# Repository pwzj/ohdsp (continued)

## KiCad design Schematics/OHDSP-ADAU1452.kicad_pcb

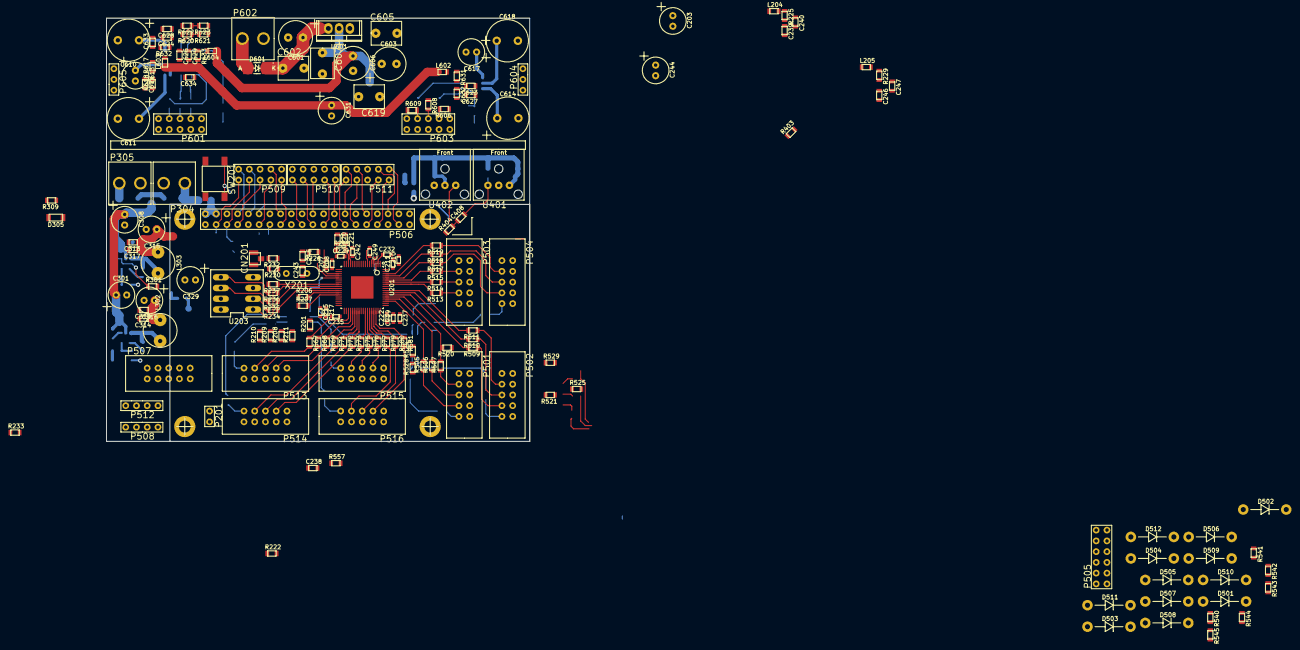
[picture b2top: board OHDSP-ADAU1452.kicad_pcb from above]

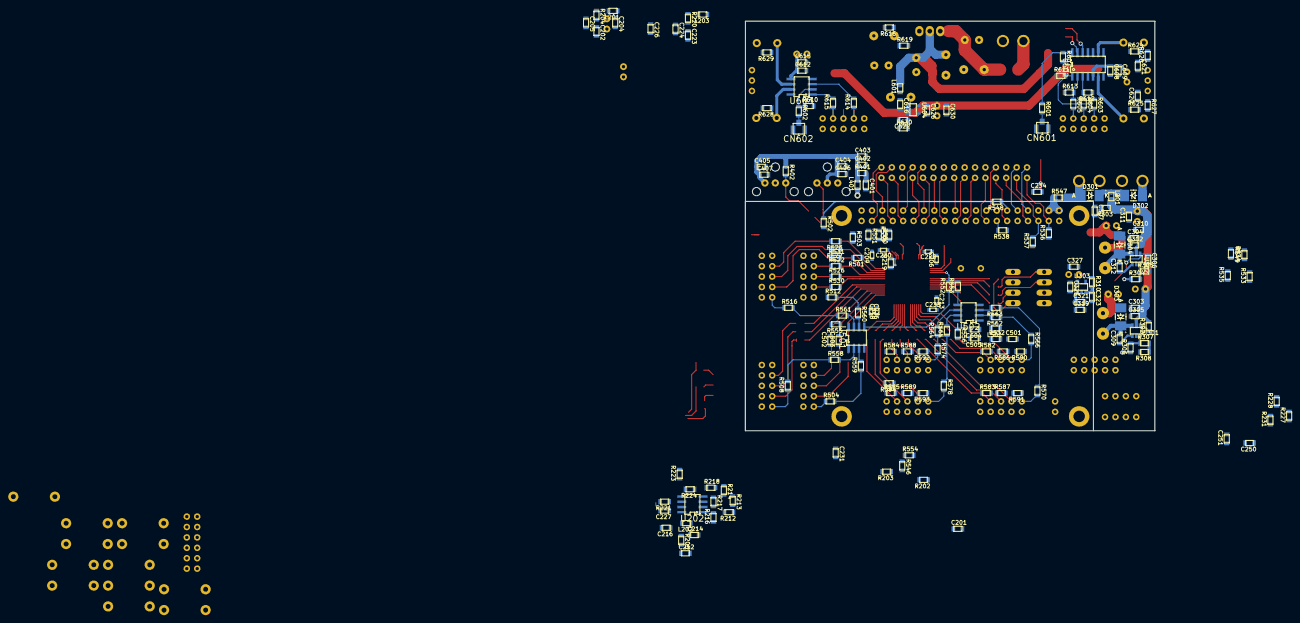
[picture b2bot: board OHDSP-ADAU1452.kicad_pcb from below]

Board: 4 copper layers, 100.0 x 100.0 mm, 376 parts (188 on the bottom side), 240 nets.

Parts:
C201, C205, C216, C226, C227, C231, C234, C238, C250, C304, C305, C311, C317, C318, C321, C325, C403, C406, C407, C503, C505, C604, C608, C612, C623, C624, C625, C626: 100n; SMD-0805
C202, C212, C223, C239, C246, C307, C401, C501, C632, C633, C634: 100p; SMD-0805
C203, C244, C301, C308, C315, C316, C329: 220u; CAP-TH-D6.3mmP2.5mm
C204, C224, C240, C247, C302, C303, C310, C313, C314, C319, C327, C402, C404, C405, C502, C504, C609, C615, C616, C627, C628, C629, C630: 22u; SMD-0805
C206, C209, C213, C218, C228, C230, C233, C236: 1u; SMD-0603
C207, C210, C215, C219, C229, C232, C235, C237, C242, C249: 100n; SMD-0603
C208, C211, C217, C222: 10n; SMD-0603
C214, C251, C306, C323: 1u; SMD-0805
C220: 5n6; SMD-0805
C221: 150p; SMD-0805
C243, C245: 33p; SMD-0805
C309, C312, C408, C622: 10n; SMD-0805
C601, C603, C606: 220u; CAP-TH-D8mmP3.5mm
C602, C605, C607, C619: 10n; CAP_TH_5mm
C610, C611, C614, C618: 100u; CAP-TH-D10mmP5mm
C613, C617, C631: 100u; CAP-TH-D6.3mmP2.5mm
C620, C621: 1n; SMD-0805
CN201, CN601, CN602: COAX; CONN-RF-UFL
D301, D302, D303, D304, D601: SS24T3G; DIODE-SMB
D305: LED; SMD-1206
D501, D502, D503, D504, D505, D506, D507, D508, D509, D510, D511, D512: 1N5818; DIODE-DO-41
L201, L202, L203, L204, L205, L301, L401, L501, L601, L602, L603, L604: 600R@100MHz; SMD-0805
L302: 744772220; PASSIVE-TH-IND-WURTH-5mm
L303: 744772047; PASSIVE-TH-IND-WURTH-5mm
P201: CONN_2x1; CONN_SIL_2
P301, P302, P303, P306: PIN; MNT_HOLE_2.5mm
P304, P305, P602: CONN_2x1; CONN-SCREW-2WAY-5mm-5.08mm
P501, P502, P503, P504, P507, P513, P514, P515, P516: CONN_02X05; CONN_DIL_2X5_BOX
P505: CONN_6X2; CONN_DIL_2X6
P506: CONN_02X20; CONN_DIL_2X20
P508, P512: CONN_4x1; CONN_SIL_4
P509, P510, P511, P601, P603: CONN_02X05; CONN_DIL_2X5
P604, P605: CONN_3x1; CONN_SIL_3
R201, R221, R538, R555, R556: 1k; SMD-0805
R202, R203, R626, R627: 2k2; SMD-0805
R204, R205, R220, R225, R229, R303, R401, R532, R631, R632, R633: 47R; SMD-0805
R206, R207, R212, R219, R234, R235, R236, R237, R308, R403, R504, R505, R506, R507, R508, R509, R510, R511, R512, R513, R514, R515, R516, R517, R518, R519, R533, R534, R535, R536, R537, R539, R546, R547, R548, R549, R550, R551, R554, R557, R601, R602, R614, R615: 0R; SMD-0805
R208, R209, R216, R230, R232, R233, R501, R502, R503, R520, R521, R522, R523, R524, R525, R526, R527, R528, R529, R530, R531, R582, R583, R584, R585, R586, R587, R588, R589, R590, R591, R592, R593, R594, R606, R607, R609, R610, R611, R612, R613, R618, R621, R623: N/F; SMD-0805
R210, R211, R227, R228, R231, R307, R402, R608, R617, R620, R622, R624, R625, R628, R629, R630: 10k; SMD-0805
R213: 12k; SMD-0805
R214: 3k3; SMD-0805
R215: 4k3; SMD-0805
R217: 3k; SMD-0805
R218: 3k6; SMD-0805
R222, R223, R226: 100R; SMD-0805
R224, R301, R302, R310: 100k; SMD-0805
R304: 47k; SMD-0805
R305: 97k6; SMD-0805
R306: 39k; SMD-0805
R309: 470R; SMD-0805
R404: 22R; SMD-0805
R540, R541, R542, R543, R544, R545: 4k7; SMD-0805
R552, R553: 75R; SMD-0805
R558, R559, R560, R561, R562, R563, R564, R565, R566, R567, R568, R569, R570, R571, R572, R573, R574, R575, R576, R577, R578, R579, R580, R581, R603, R604, R605: 27R; SMD-0805
R616: 360R; SMD-0805
R619: 120R; SMD-0805
SW201: SWITCH; SW_TACT_SMD
U201: ADAU1452WBCPZ; IC-LFCSP72-HANDFIT
U202: ADM13307-5ARZ; IC_SOIC_8
U203: 25AA1024; IC_DIP_8
U301, U302: IC-REG-XRP7659ISTR-F; IC-SOT23-6
U303, U604: IC-REG-XC6210B332MR; IC-SOT25
U401: IC-SPDIF-RX-OPTO; IC_SPDIF_OPTO
U402: IC-SPDIF-TX-OPTO; IC_SPDIF_OPTO
U501, U502: NB3L553; IC_SOIC_8
U601: IC-REG-LM317-TO220; TO-220
U602: IC-DAC-WM8501; IC_SOIC_14
U603: IC-ADC-WM8783; IC_SOIC_8
X201: 24M576; XTAL_HC49_TH

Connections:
+5V: D301.1, P304.1, R547.2
/ADAU1452/ADAU_SPDIF_RX: R404.1, U201.4
/ADAU1452/ADAU_SPDIF_TX: R403.1, U201.5
/ADAU1452/ADCIN_BCLK0: R506.2, R524.2, U201.58
/ADAU1452/ADCIN_BCLK1: R510.2, R525.2, U201.61
/ADAU1452/ADCIN_BCLK2: R514.2, R526.2, U201.66
/ADAU1452/ADCIN_BCLK3: R502.2, R518.2, R527.2, U201.69
/ADAU1452/ADCIN_LRCLK0: R505.2, R528.2, U201.57
/ADAU1452/ADCIN_LRCLK1: R509.2, R529.2, U201.60
/ADAU1452/ADCIN_LRCLK2: R513.2, R530.2, U201.65
/ADAU1452/ADCIN_LRCLK3: R501.2, R517.2, R531.2, U201.68
/ADAU1452/ADCIN_SDATA0: R507.2, R520.2, U201.59
/ADAU1452/ADCIN_SDATA1: R511.2, R521.2, U201.62
/ADAU1452/ADCIN_SDATA2: R515.2, R522.2, U201.67
/ADAU1452/ADCIN_SDATA3: R503.2, R519.2, R523.2, U201.70
/ADAU1452/AVDD: C247.1, C249.1, L205.2, R229.1, U201.7
/ADAU1452/DACOUT_BCLK0: R568.1, U201.40
/ADAU1452/DACOUT_BCLK1: R572.1, U201.43
/ADAU1452/DACOUT_BCLK2: R576.1, U201.48
/ADAU1452/DACOUT_BCLK3: R580.1, U201.51
/ADAU1452/DACOUT_LRCLK0: R567.1, U201.39
/ADAU1452/DACOUT_LRCLK1: R571.1, U201.42
/ADAU1452/DACOUT_LRCLK2: R575.1, U201.47
/ADAU1452/DACOUT_LRCLK3: R579.1, U201.50
/ADAU1452/DACOUT_SDATA0: R569.1, U201.41
/ADAU1452/DACOUT_SDATA1: R573.1, U201.44
/ADAU1452/DACOUT_SDATA2: R577.1, U201.49
/ADAU1452/DACOUT_SDATA3: R581.1, U201.52
/ADAU1452/DSP_RESET: C238.1, R222.1, U201.24
/ADAU1452/DVDD: C203.1, C204.1, C205.1, C206.1, C207.1, C208.1, C209.1, C210.1, C211.1, C213.1, C215.1, C217.1, C218.1, C219.1, C222.1, L201.2, R204.1, U201.20, U201.35, U201.53, U201.71
/ADAU1452/GLB_RESET: R223.1, R546.1, R557.1
/ADAU1452/I2C_SCL: P507.1, P508.1, P512.1, R202.2, R207.1, R537.1
/ADAU1452/I2C_SDA: P507.3, P508.2, P512.2, R203.2, R206.1, R536.1
/ADAU1452/IOVDD: C224.1, C226.1, C228.1, C229.1, C230.1, C232.1, C233.1, C235.1, C236.1, C237.1, L203.2, R208.1, R209.1, R220.1, U201.2, U201.18, U201.38, U201.56
/ADAU1452/MAN_RST_IN: C234.1, R221.2, R538.1, R554.2, SW201.1
/ADAU1452/MCLK: R552.2, R553.2, U201.23
/ADAU1452/M_MISO: R233.2, R234.2, U203.2
/ADAU1452/M_MOSI: R236.2, U203.5
/ADAU1452/M_SCLK: R235.2, U203.6
/ADAU1452/M_SS: R227.2, R237.2, U203.1
/ADAU1452/PVDD: C220.1, C221.1, C240.1, C242.1, L204.2, R225.1, U201.15
/ADAU1452/SELFBOOT: P201.1, R201.2, U201.34
/ADAU1452/XTALIN: C243.1, R230.1, R232.1, U201.21, X201.1
/ADAU1452/XTALOUT: R226.1, U201.22
/Connectors/AUXADCIN_1: D501.1, D502.2, R540.2, U201.8
/Connectors/AUXADCIN_2: D503.1, D504.2, R541.2, U201.9
/Connectors/AUXADCIN_3: D505.1, D506.2, R542.2, U201.10
/Connectors/AUXADCIN_4: D507.1, D508.2, R543.2, U201.11
/Connectors/AUXADCIN_5: D509.1, D510.2, R544.2, U201.12
/Connectors/AUXADCIN_6: D511.1, D512.2, R545.2, U201.13
/Connectors/MCLKA1: R508.2, R558.1
/Connectors/MCLKA2: R504.2, R559.1
/Connectors/MCLKA3: R512.2, R560.1
/Connectors/MCLKA4: R516.2, R561.1
/Connectors/MCLKB1: R562.1, R566.1
/Connectors/MCLKB2: R563.1, R570.1
/Connectors/MCLKB3: R564.1, R574.1
/Connectors/MCLKB4: R565.1, R578.1
/Connectors/PI_GP4: P506.7, P509.5
/Connectors/PI_GP5: P506.29, P511.3
/Connectors/PI_GP6: P506.31, P511.7
/Connectors/PI_GP12: P506.32, P511.4
/Connectors/PI_GP13: P506.33, P511.9
/Connectors/PI_GP14: P506.8, P509.2
/Connectors/PI_GP15: P506.10, P509.4
/Connectors/PI_GP16: P506.36, P511.8
/Connectors/PI_GP17: P506.11, P509.7
/Connectors/PI_GP22: P506.15, P509.9
/Connectors/PI_GP23: P506.16, P509.8
/Connectors/PI_GP24: P506.18, P509.10
/Connectors/PI_GP25: P506.22, P510.5
/Connectors/PI_GP26: P506.37, P511.10
/Connectors/PI_IDSC: P506.28, P511.2
/Connectors/PI_IDSD: P506.27, P511.1
/Connectors/PI_MISO: P506.21, P510.3, R534.2
/Connectors/PI_MOSI: P506.19, P510.1, R533.2
/Connectors/PI_SCL: P506.5, P509.3, R537.2
/Connectors/PI_SCLK: P506.23, P510.7, R535.2
/Connectors/PI_SDA: P506.3, P509.1, R536.2
/Connectors/RPI_BCLK: R502.1, R548.2
/Connectors/RPI_CS2: P506.26, P510.9
/Connectors/RPI_LRCLK: R501.1, R539.1
/Connectors/RPI_SDATA_IN: R550.2, R594.2
/Connectors/RPI_SDATA_OUT: R503.1, R551.2
/SimpleADCDAC/ADC_AVDD: C623.1, C627.1, L602.2, R631.1, U603.8
/SimpleADCDAC/DAC5v: C606.1, C607.1, L601.2, L604.1, R619.2, U601.2
/SimpleADCDAC/DAC_AVDD: C625.1, C629.1, L604.2, R633.1, U602.8
/SimpleADCDAC/DAC_DVDD: C624.1, C628.1, L603.2, R617.2, R620.2, R622.2, R632.1, U602.11
/SimpleADCDAC/DEMP: R622.1, R623.2, U602.12
/SimpleADCDAC/EN: C604.1, R617.1, R618.2, U602.4
/SimpleADCDAC/FMT: R620.1, R621.2, U602.13
GNDA: C601.2, C602.2, C603.2, C604.2, C605.2, C606.2, C607.2, C608.2, C609.2, C612.2, C613.2, C615.2, C616.2, C617.2, C619.2, C620.2, C621.2, C622.2, C623.2, C624.2, C625.2, C626.2, C627.2, C628.2, C629.2, C630.2, C631.2, C632.2, C633.2, C634.2, CN601.2, CN602.2, P601.1, P601.2, P601.3, P601.5, P601.7, P601.9, P601.10, P602.2, P603.1, P603.2, P603.3, P603.5, P603.7, P603.9, P603.10, P604.2, P605.2, R606.1, R607.2, R608.1, R609.1, R610.2, R611.1, R612.1, R613.1, R616.2, R618.1, R621.1, R623.1, R624.1, R625.1, R628.1, R629.1, U602.7, U602.10, U603.4, U604.2
GNDD: C201.2, C202.2, C203.2, C204.2, C205.2, C206.2, C207.2, C208.2, C209.2, C210.2, C211.2, C212.2, C213.2, C214.2, C215.2, C216.2, C217.2, C218.2, C219.2, C222.2, C223.2, C224.2, C226.2, C227.2, C228.2, C229.2, C230.2, C231.2, C232.2, C233.2, C234.2, C235.2, C236.2, C237.2, C238.2, C239.2, C240.2, C242.2, C243.2, C244.2, C245.2, C246.2, C247.2, C249.2, C250.2, C251.2, C301.2, C302.1, C303.1, C304.1, C305.1, C306.2, C307.2, C308.2, C310.1, C311.1, C313.2, C314.2, C315.2, C316.2, C317.2, C318.2, C319.2, C321.2, C323.2, C325.2, C327.2, C329.2, C401.2, C402.2, C403.2, C404.2, C405.2, C406.2, C407.2, C501.2, C502.2, C503.2, C504.2, C505.2, CN201.2, D303.1, D304.1, D305.2, D502.1, D504.1, D506.1, D508.1, D510.1, D512.1, P201.2, P301.1, P302.1, P303.1, P304.2, P305.2, P306.1, P501.1, P501.3, P501.5, P501.7, P501.9, P501.10, P502.1, P502.3, P502.5, P502.7, P502.9, P502.10, P503.1, P503.3, P503.5, P503.7, P503.9, P503.10, P504.1, P504.3, P504.5, P504.7, P504.9, P504.10, P505.1, P505.3, P505.5, P505.7, P505.9, P505.11, P506.6, P506.9, P506.14, P506.20, P506.25, P506.30, P506.34, P506.39, P508.3, P509.6, P510.2, P510.4, P510.6, P510.8, P510.10, P511.5, P511.6, P512.3, P513.1, P513.3, P513.5, P513.7, P513.9, P513.10, P514.1, P514.3, P514.5, P514.7, P514.9, P514.10, P515.1, P515.3, P515.5, P515.7, P515.9, P515.10, P516.1, P516.3, P516.5, P516.7, P516.9, P516.10, R210.1, R211.1, R216.1, R217.1, R218.1, R219.1, R224.1, R230.2, R305.2, R308.2, R520.1, R521.1, R522.1, R523.1, R524.1, R525.1, R526.1, R527.1, R528.1, R529.1, R530.1, R531.1, R582.1, R583.1, R584.1, R585.1, R586.1, R587.1, R588.1, R589.1, R590.1, R591.1, R592.1, R593.1, SW201.2, U201.1, U201.6, U201.14, U201.17, U201.19, U201.25, U201.36, U201.37, U201.54, U201.55, U201.72, U201.EP1, U202.4, U203.4, U301.2, U302.2, U303.2, U401.2, U402.3, U501.4, U502.4
unnamed: C202.1, R204.2
unnamed: C212.1, R205.2
unnamed: C214.1, C216.1, L202.2, R205.1, U202.8
unnamed: C220.2, R215.1
unnamed: C221.2, R215.2, U201.16
unnamed: C223.1, R220.2
unnamed: C227.1, R221.1, U202.7
unnamed: C231.1, R222.2, R223.2, R224.2, U202.6
unnamed: C239.1, R225.2
unnamed: C245.1, R226.2, X201.2
unnamed: C246.1, R229.2
unnamed: C306.1, R301.1, U302.4
unnamed: C307.1, R303.2
unnamed: C309.1, U301.1
unnamed: C309.2, D303.2, L302.1, U301.6
unnamed: C312.1, U302.1
unnamed: C312.2, D304.2, L303.1, U302.6
unnamed: C323.1, R310.2, U303.3
unnamed: C401.1, R401.2
unnamed: C402.1, C403.1, C404.1, C405.1, C406.1, C407.1, L401.2, R401.1, R402.1, U401.1, U402.2
unnamed: C408.1, R404.2
unnamed: C408.2, R402.2, U401.3
unnamed: C501.1, R532.2
unnamed: C502.1, C503.1, C504.1, C505.1, L501.2, R532.1, R555.2, R556.2, U501.1, U502.1
unnamed: C601.1, C602.1, D601.2, U601.3
unnamed: C603.1, C605.1, R616.1, R619.1, U601.1
unnamed: C608.1, C609.1, C613.1, U602.5
unnamed: C610.1, U602.9
unnamed: C610.2, R624.2, R626.2
unnamed: C611.1, U602.6
unnamed: C611.2, R625.2, R627.2
unnamed: C612.1, C615.1, C617.1, U603.5
unnamed: C614.1, U603.7
unnamed: C614.2, P604.1, R628.2
unnamed: C616.1, C619.1, L601.1, R630.1, U604.1
unnamed: C618.1, U603.6
unnamed: C618.2, P604.3, R629.2
unnamed: C620.1, P605.3, R627.1
unnamed: C621.1, P605.1, R626.1
unnamed: C622.1, R630.2, U604.3
unnamed: C626.1, C630.1, C631.1, L602.1, L603.1, U604.5
unnamed: C632.1, R631.2
unnamed: C633.1, R632.2
unnamed: C634.1, R633.2
unnamed: CN201.1, R232.2
unnamed: CN601.1, R601.2
unnamed: CN602.1, R602.2
unnamed: D301.2, D302.2, L301.1
unnamed: D302.1, P305.1
unnamed: D305.1, R309.2
unnamed: D601.1, P602.1
unnamed: P501.2, R504.1
unnamed: P501.4, R505.1
unnamed: P501.6, R506.1
unnamed: P501.8, R507.1
unnamed: P502.2, R508.1
unnamed: P502.4, R509.1
unnamed: P502.6, R510.1
unnamed: P502.8, R511.1
unnamed: P503.2, R512.1
unnamed: P503.4, R513.1
unnamed: P503.6, R514.1
unnamed: P503.8, R515.1
unnamed: P504.2, R516.1
unnamed: P504.4, R517.1
unnamed: P504.6, R518.1
unnamed: P504.8, R519.1
unnamed: P505.2, R540.1
unnamed: P505.4, R541.1
unnamed: P505.6, R542.1
unnamed: P505.8, R543.1
unnamed: P505.10, R544.1
unnamed: P505.12, R545.1
unnamed: P506.2, P506.4, R547.1
unnamed: P506.12, R548.1
unnamed: P506.13, R538.2
unnamed: P506.24, R549.1
unnamed: P506.35, R539.2
unnamed: P506.38, R550.1
unnamed: P506.40, R551.1
unnamed: P507.6, R554.1
unnamed: P508.4, R546.2
unnamed: P512.4, R557.2
unnamed: P513.2, R566.2
unnamed: P513.4, R567.2, R590.2
unnamed: P513.6, R568.2, R586.2
unnamed: P513.8, R569.2, R582.2
unnamed: P514.2, R570.2
unnamed: P514.4, R571.2, R591.2
unnamed: P514.6, R572.2, R587.2
unnamed: P514.8, R573.2, R583.2
unnamed: P515.2, R574.2
unnamed: P515.4, R575.2, R592.2
unnamed: P515.6, R576.2, R588.2
unnamed: P515.8, R577.2, R584.2
unnamed: P516.2, R578.2
unnamed: P516.4, R579.2, R593.2
unnamed: P516.6, R580.2, R589.2
unnamed: P516.8, R581.2, R585.2, R594.1
unnamed: P601.4, R603.2
unnamed: P601.6, R604.2
unnamed: P601.8, R605.2
unnamed: P603.4, R609.2, R614.1
unnamed: P603.6, R608.2
unnamed: P603.8, R606.2, R615.1
unnamed: R206.2, U201.30
unnamed: R207.2, U201.31
unnamed: R208.2, R211.2, U201.33
unnamed: R209.2, R210.2, U201.32
unnamed: R212.2, R216.2, U202.1
unnamed: R213.2, R217.2, U202.2
unnamed: R214.2, R218.2, U202.3
unnamed: R219.2, U201.3
unnamed: R228.2, U203.3
unnamed: R231.2, U203.7
unnamed: R234.1, U201.29
unnamed: R235.1, U201.28
unnamed: R236.1, U201.27
unnamed: R237.1, U201.26
unnamed: R302.1, U301.4
unnamed: R304.2, R305.1, U302.3
unnamed: R306.2, R307.1, U301.3
unnamed: R307.2, R308.1
unnamed: R403.2, U402.1
unnamed: R552.1, U501.5
unnamed: R553.1, U502.5
unnamed: R555.1, U501.8
unnamed: R556.1, U502.8
unnamed: R558.2, U501.2
unnamed: R559.2, U501.3
unnamed: R560.2, U501.6
unnamed: R561.2, U501.7
unnamed: R562.2, U502.2
unnamed: R563.2, U502.3
unnamed: R564.2, U502.6
unnamed: R565.2, U502.7
unnamed: R601.1, R607.1, U602.14
unnamed: R602.1, R610.1, U603.2
unnamed: R603.1, R611.2, U602.1
unnamed: R604.1, R612.2, U602.3
unnamed: R605.1, R613.2, U602.2
unnamed: R614.2, U603.3
unnamed: R615.2, U603.1
VAA: C201.1, C244.1, C250.1, C251.1, C325.1, C327.1, C329.1, D501.2, D503.2, D505.2, D507.2, D509.2, D511.2, L202.1, L203.1, L204.1, L205.1, L401.1, L501.1, R201.1, R202.1, R203.1, R212.1, R213.1, R227.1, R228.1, R231.1, R233.1, R301.2, R309.1, U203.8, U303.5
VCC: C301.1, C302.2, C303.2, C304.2, C305.2, C308.1, C310.2, C311.2, L301.2, R302.2, R303.1, U301.5, U302.5
VCOM: C314.1, C316.1, C318.1, C319.1, C321.1, L302.2, R306.1, R310.1, U303.1
VDD: C313.1, C315.1, C317.1, L201.1, L303.2, R214.1, R304.1

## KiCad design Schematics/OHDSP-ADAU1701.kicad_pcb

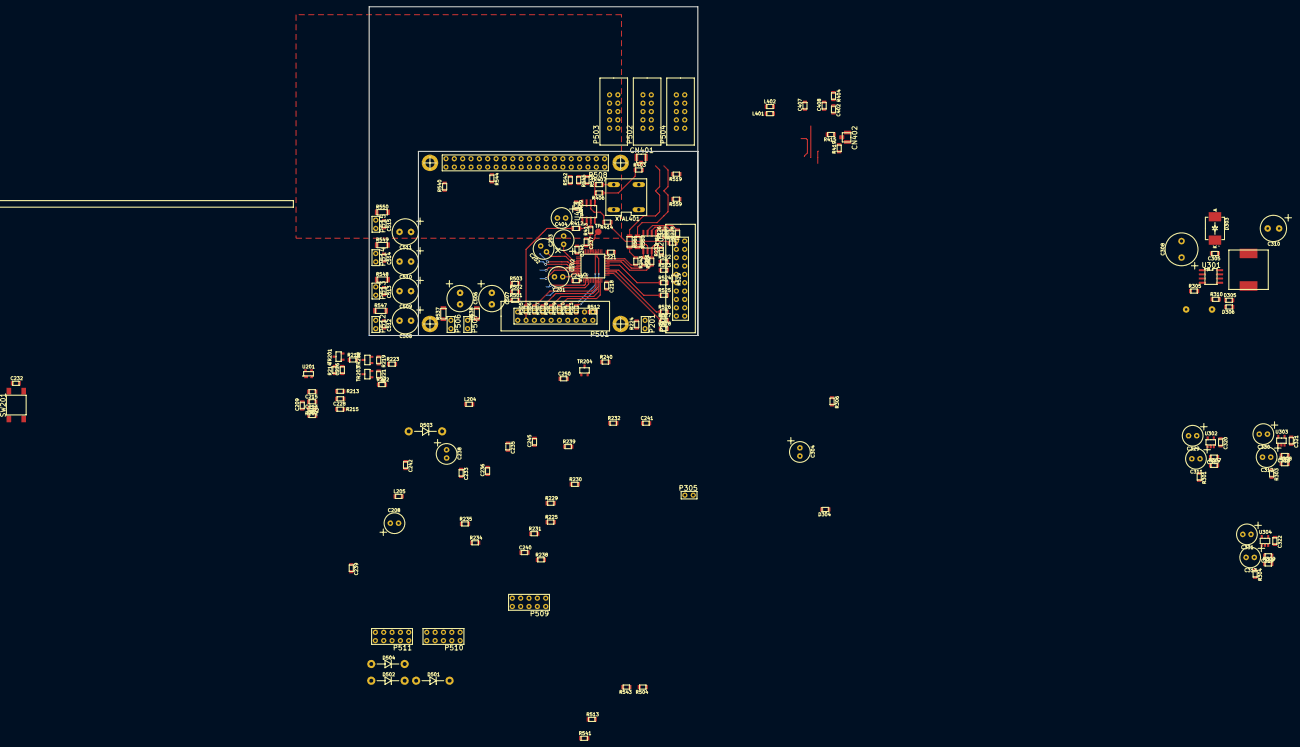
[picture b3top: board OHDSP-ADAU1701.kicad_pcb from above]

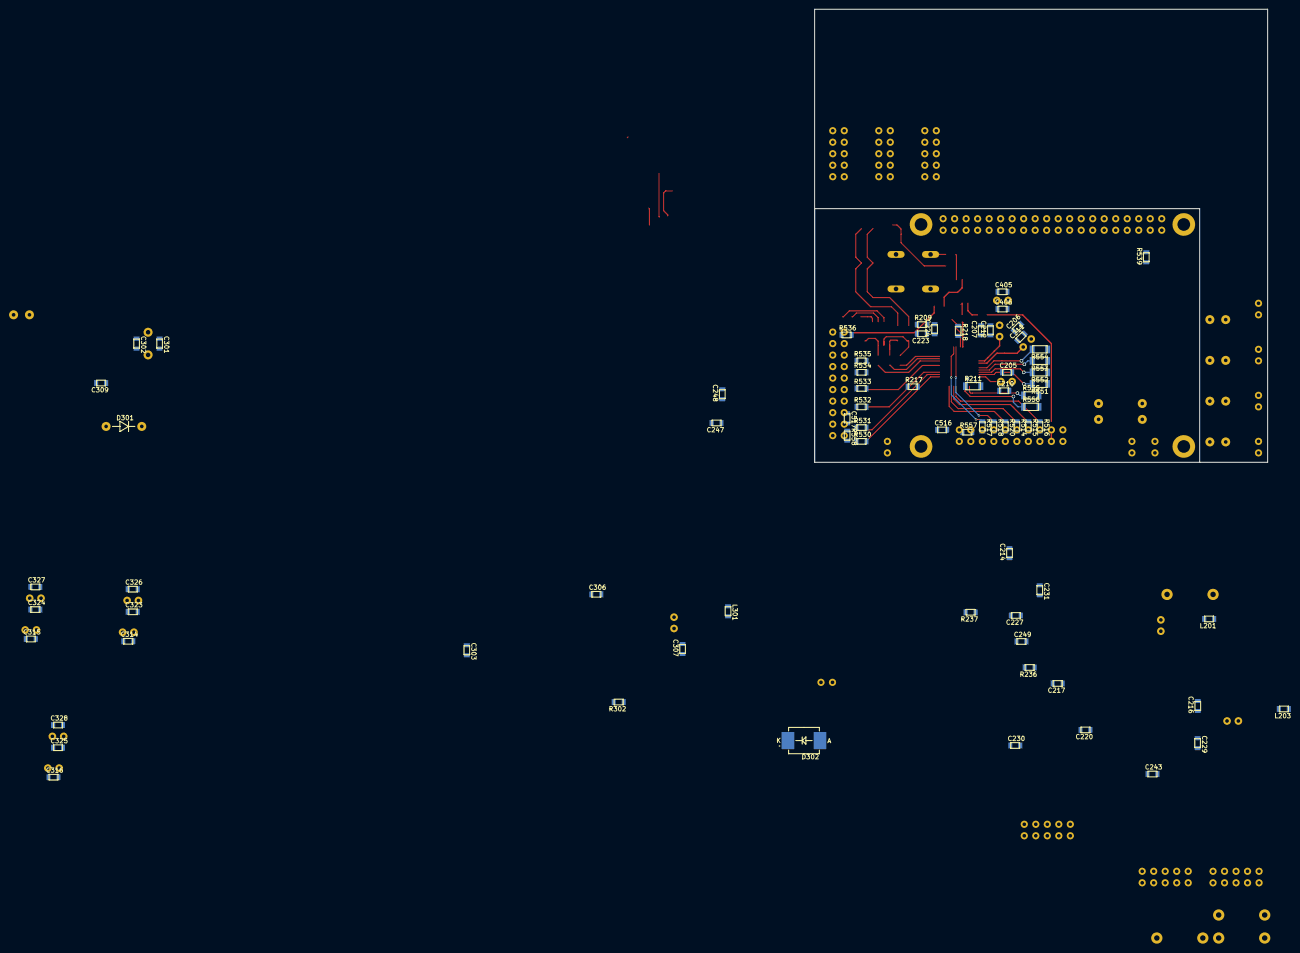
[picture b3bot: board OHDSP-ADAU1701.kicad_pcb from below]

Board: 4 copper layers, 100.0 x 100.0 mm, 265 parts (73 on the bottom side), 172 nets.

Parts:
C201, C202, C203, C208, C238, C304, C311, C312, C313, C329, C330, C331, C404: 220u; CAP-TH-D6.3mmP2.5mm
C205, C206, C207: 10u; SMD-0805
C209, C239, C303, C516, C517: 100p; SMD-0805
C210, C211, C212, C215, C216, C218, C221, C226, C228, C230, C232, C233, C237, C242, C244, C246, C247, C249, C302, C307, C314, C315, C316, C320, C321, C322, C323, C324, C325, C402, C406, C407: 100n; SMD-0805
C213, C217, C220, C231, C243, C245, C248: 1u; SMD-0805
C214, C227, C229, C235, C236, C240, C241, C301, C306, C326, C327, C328, C405, C408: 22u; SMD-0805
C223: 56n; SMD-0805
C224: 3n3; SMD-0805
C250: N/F; SMD-0805
C305: 270n; SMD-0805
C308: 35ZL470MEFC10X20; CAP-TH-D10mmP5mm
C309: 1n5; SMD-0805
C310: 10ZL470MEFC8X11.5; CAP-TH-D8mmP3.5mm
C317, C318, C319: 10n; SMD-0805
C506, C507: 47u; CAP-TH-D8mmP3.5mm
C508, C509, C510, C511: 220u; CAP-TH-D8mmP3.5mm
C512, C513, C514, C515: 5n6; SMD-0805
CN401, CN402: COAX; CONN-RF-UFL
D301: 1N914; DIODE-DO-35
D302, D303: MBRS330T3; DIODE-SMC
D304, D305, D306: LED; SMD-0805
D501, D502, D503, D504: 1N5818; DIODE-DO-41
L201, L202, L203, L204, L205, L301, L401, L402: 600R@100MHz; SMD-0805
L302: CDRH125NP-100MC; IND_SMD_CDRH125
P201, P305, P506, P507, P512, P513, P514, P515: CONN_2x1; CONN_SIL_2
P301, P302, P303, P306: PIN; MNT_HOLE_2.5mm
P501, P505: CONN_02X10; CONN_DIL_2X10_BOX
P502, P503, P504: CONN_02X05; CONN_DIL_2X5_BOX
P508: CONN_02X20; CONN_DIL_2X20
P509, P510, P511: CONN_02X05; CONN_DIL_2X5
R202, R225, R302, R557, R558: 47R; SMD-0805
R209: 475R; SMD-0805
R211: 7k5; SMD-1206
R213, R217, R218, R226, R227, R228, R241, R242, R243, R505, R506, R507, R508, R509, R510, R511, R512, R528, R539, R540, R542, R544, R545, R546: 0R; SMD-0805
R214, R216, R224, R235, R238, R404, R409, R513, R519, R541, R559: 1k; SMD-0805
R215, R219, R221: 100k; SMD-0805
R222, R223, R230, R231, R233, R307, R308, R309: 10k; SMD-0805
R229, R232, R234, R239, R240, R403, R406, R419, R501, R502, R503, R504, R514, R515, R516, R517, R518, R520, R529, R530, R531, R532, R533, R534, R535, R536, R543: N/F; SMD-0805
R236, R237: 2k2; SMD-0805
R301, R303, R304: 1R; SMD-0805
R305, R310: 4k7; SMD-0805
R306: 470R; SMD-0805
R407, R415, R521, R522, R523, R524, R525, R526, R527: 27R; SMD-0805
R412, R413, R414: 75R; SMD-0805
R537, R538: 18k; SMD-1206
R547, R548, R549, R550: 560R; SMD-1206
R551, R552, R553, R554, R555, R556, R560, R561: 0R; SMD-1206
SW201: SWITCH; SW_TACT_SMD
TP201: TP; TP-2mm
TR201: BC847; IC-SOT23
TR202, TR203: BC857; IC-SOT23
TR204: N/F; IC-SOT23
U201: IC-RST-ADM811; IC-SOT143
U202: ADAU1701JSTZ; IC-LQFP48_7x7
U203: IC-EEPROM-I2C; IC_SOIC_8
U301: LT1374CS8-5#PBF; IC_SOIC_8
U302, U303: NCP700BSN33T1G; IC-SOT23-5
U304: NCP700BSN18T1G; IC-SOT23-5
U403: NB3L553; IC_SOIC_8
XTAL401: XTAL-OSC-4PIN; XTAL_8_DIL

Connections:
+5V: C310.1, D301.1, L302.2, R301.2, R303.2, R304.2, R306.1, R543.2, U301.3, U301.5
/ADAU1701/ADCIN_BCLK0: R502.2, R507.2, U202.9
/ADAU1701/ADCIN_LRCLK0: R501.2, R506.2, U202.8
/ADAU1701/ADCIN_SDATA0: R503.2, R508.2, U202.10
/ADAU1701/ADCIN_SDATA1: R509.2, U202.11
/ADAU1701/ADCIN_SDATA2: R510.2, U202.29
/ADAU1701/ADCIN_SDATA3: R511.2, U202.28
/ADAU1701/ADC_IN0: R555.1, U202.2
/ADAU1701/ADC_IN1: R556.1, U202.4
/ADAU1701/ADDR0: R229.1, R230.1, U202.7
/ADAU1701/ADDR1: R231.1, R232.1, TR204.3, U202.20
/ADAU1701/AVDD: C238.1, C240.1, C241.1, C242.1, C243.1, C244.1, C245.1, C246.1, L205.2, R225.1, U202.36, U202.48
/ADAU1701/CM: C203.1, C207.1, C212.1, U202.40
/ADAU1701/DACOUT_BCLK0: R524.1, R533.2, U202.19
/ADAU1701/DACOUT_LRCLK0: R525.1, R532.2, U202.16
/ADAU1701/DACOUT_SDATA0: R526.1, R531.2, U202.15
/ADAU1701/DACOUT_SDATA1: R527.1, R530.2, U202.14
/ADAU1701/DACOUT_SDATA2: R523.1, R534.2, U202.27
/ADAU1701/DACOUT_SDATA3: R522.1, R535.2, U202.26
/ADAU1701/DVDD: C208.1, C214.1, C216.1, C217.1, C218.1, C220.1, C221.1, C250.1, L201.2, R240.2, U202.13, U202.24
/ADAU1701/FILTA: C201.1, C205.1, C210.1, U202.47
/ADAU1701/FILTD: C202.1, C206.1, C211.1, U202.41
/ADAU1701/I2C_SCL: R237.2, R243.1, R561.2, U203.6
/ADAU1701/I2C_SDA: R236.2, R242.1, R560.2, U203.5
/ADAU1701/IOVDD: C227.1, C229.1, C230.1, C231.1, C233.1, C247.1, C248.1, L203.2, R226.1, R227.1, R228.1, R229.2, R231.2, R233.1, R234.2, R238.1, U202.18, U203.8
/ADAU1701/MCLK: R413.1, U202.32
/ADAU1701/PLL0: R234.1, R235.1, U202.38
/ADAU1701/PLL1: R238.2, R239.2, U202.39
/ADAU1701/PVDD: C224.2, C235.1, C236.1, C237.1, L204.2, R209.2, U202.34
/ADAU1701/SELFBOOT: P201.1, R224.2, U202.6
/ADAU1701/WP: R241.1, U202.21
/ClockFanout/CLK: R406.2, R407.1, U403.5
/ClockFanout/MCLKB1: R412.2, U403.2
/ClockFanout/MCLKB2: R413.2, U403.3
/ClockFanout/MCLKB3: R414.2, U403.6
/ClockFanout/MCLKB4: R415.2, U403.7
/ClockFanout/MCLKC4: CN402.1, R415.1, R419.2
/Connectors/ADC_MCLK: R412.1, R504.2, R505.2
/Connectors/ADC_RESET: C228.1, R213.2, R215.2, R512.2, R519.1, R528.1, R559.1, U202.5
/Connectors/ADI_RST: R222.2, R513.1
/Connectors/ANA_OUT1: R551.2, U202.46
/Connectors/ANA_OUT2: R552.2, U202.45
/Connectors/ANA_OUT3: R553.2, U202.44
/Connectors/ANA_OUT4: R554.2, U202.43
/Connectors/DAC_MCLK: R414.1, R521.1, R536.2
/Connectors/PI_CS1: P508.24, P510.9
/Connectors/PI_CS2: P508.26, P511.1
/Connectors/PI_GP4: P508.7, P509.5
/Connectors/PI_GP5: P508.29, P511.5
/Connectors/PI_GP6: P508.31, P511.7
/Connectors/PI_GP12: P508.32, P511.4
/Connectors/PI_GP13: P508.33, P511.9
/Connectors/PI_GP14: P508.8, P509.2
/Connectors/PI_GP15: P508.10, P509.4
/Connectors/PI_GP16: P508.36, P511.8
/Connectors/PI_GP17: P508.11, P509.7
/Connectors/PI_GP22: P508.15, P509.9
/Connectors/PI_GP23: P508.16, P509.8
/Connectors/PI_GP24: P508.18, P509.10
/Connectors/PI_GP25: P508.22, P510.5
/Connectors/PI_GP26: P508.37, P511.10
/Connectors/PI_IDSC: P508.28, P511.2
/Connectors/PI_IDSD: P508.27, P511.3
/Connectors/PI_MISO: P508.21, P510.3
/Connectors/PI_MOSI: P508.19, P510.1
/Connectors/PI_RST: R223.2, R541.1
/Connectors/PI_SCL: P508.5, P509.3, R540.2
/Connectors/PI_SCLK: P508.23, P510.7
/Connectors/PI_SDA: P508.3, P509.1, R539.2
/Connectors/RPI_BCLK: R502.1, R544.2
/Connectors/RPI_LRCLK: R501.1, R542.1
/Connectors/RPI_SDATA_IN: R529.1, R545.2
/Connectors/RPI_SDATA_OUT: R503.1, R546.2
/Connectors/SL_SCL: P502.1, P503.1, P504.1, R540.1, R561.1
/Connectors/SL_SDA: P502.3, P503.3, P504.3, R539.1, R560.1
GNDD: C201.2, C202.2, C203.2, C205.2, C206.2, C207.2, C208.2, C209.2, C210.2, C211.2, C212.2, C213.2, C214.2, C215.2, C216.2, C217.2, C218.2, C220.2, C221.2, C226.2, C227.2, C228.2, C229.2, C230.2, C231.2, C232.2, C233.2, C235.2, C236.2, C237.2, C238.2, C239.2, C240.2, C241.2, C242.2, C243.2, C244.2, C245.2, C246.2, C247.2, C248.2, C249.2, C250.2, C301.1, C302.1, C303.2, C304.2, C306.1, C307.1, C308.2, C309.1, C310.2, C311.2, C312.2, C313.2, C314.2, C315.2, C316.2, C317.2, C318.2, C319.2, C320.2, C321.2, C322.2, C323.2, C324.2, C325.2, C326.2, C327.2, C328.2, C329.2, C330.2, C331.2, C402.2, C404.2, C405.2, C406.2, C407.2, C408.2, C512.2, C513.2, C514.2, C515.2, C516.1, C517.1, CN401.2, CN402.2, D303.1, D304.2, D306.2, D501.1, D502.1, P201.2, P301.1, P302.1, P303.1, P305.2, P306.1, P501.1, P501.3, P501.5, P501.7, P501.9, P501.11, P501.13, P501.15, P501.17, P501.19, P502.10, P503.10, P504.10, P505.2, P505.4, P505.6, P505.8, P505.10, P505.12, P505.14, P505.16, P505.18, P505.20, P506.2, P507.2, P508.6, P508.9, P508.14, P508.20, P508.25, P508.30, P508.34, P508.39, P509.6, P510.2, P510.4, P510.6, P510.8, P510.10, P511.6, P512.2, P513.2, P514.2, P515.2, R211.2, R215.1, R217.1, R218.1, R230.2, R232.2, R235.2, R239.1, R403.2, R419.1, R504.1, R514.1, R515.1, R516.1, R517.1, R518.1, R520.1, R530.1, R531.1, R532.1, R533.1, R534.1, R535.1, R536.1, SW201.2, TR201.2, TR204.2, U201.1, U202.1, U202.12, U202.25, U202.33, U202.37, U202.42, U203.4, U301.4, U302.2, U303.2, U304.2, U403.4, XTAL401.2
unnamed: C209.1, R202.2
unnamed: C213.1, C215.1, L202.2, R202.1, U201.4
unnamed: C223.1, C224.1, U202.35
unnamed: C223.2, R209.1
unnamed: C226.1, R214.1, U201.3
unnamed: C232.1, R214.2, SW201.1, TR201.3
unnamed: C239.1, R225.2
unnamed: C303.1, R302.2
unnamed: C305.1, D303.2, L302.1, U301.8
unnamed: C305.2, D301.2, U301.2
unnamed: C309.2, U301.6
unnamed: C311.1, C314.1, R301.1, R307.1, U302.1
unnamed: C312.1, C315.1, R303.1, R308.1, U303.1
unnamed: C313.1, C316.1, R304.1, R309.1, U304.1
unnamed: C317.1, R307.2, U302.3
unnamed: C318.1, R308.2, U303.3
unnamed: C319.1, R309.2, U304.3
unnamed: C320.1, U302.4
unnamed: C321.1, U303.4
unnamed: C322.1, U304.4
unnamed: C402.1, R404.2, XTAL401.1
unnamed: C404.1, C405.1, C406.1, L401.2, R409.2, U403.1
unnamed: C407.1, C408.1, L402.2, R404.1, XTAL401.4
unnamed: C506.1, D501.2, D503.1, R555.2
unnamed: C506.2, R537.2
unnamed: C507.1, D502.2, D504.1, R556.2
unnamed: C507.2, R538.2
unnamed: C508.1, R551.1
unnamed: C508.2, R547.2
unnamed: C509.1, R552.1
unnamed: C509.2, R548.2
unnamed: C510.1, R553.1
unnamed: C510.2, R549.2
unnamed: C511.1, R554.1
unnamed: C511.2, R550.2
unnamed: C512.1, P512.1, R547.1
unnamed: C513.1, P513.1, R548.1
unnamed: C514.1, P514.1, R549.1
unnamed: C515.1, P515.1, R550.1
unnamed: C516.2, R557.1
unnamed: C517.2, R558.1
unnamed: CN401.1, R403.1, R406.1
unnamed: D302.1, P305.1
unnamed: D302.2, L301.1
unnamed: D304.1, R306.2
unnamed: D305.1, R305.2, R310.2, U301.7
unnamed: D305.2, D306.1
unnamed: P501.2, R505.1
unnamed: P501.4, R506.1, R516.2
unnamed: P501.6, R507.1, R515.2
unnamed: P501.8, R508.1, R514.2
unnamed: P501.10, R509.1, R520.2
unnamed: P501.12, R510.1, R518.2
unnamed: P501.14, R511.1, R517.2
unnamed: P501.18, R512.1, R557.2
unnamed: P502.6, R519.2
unnamed: P503.6, R559.2
unnamed: P504.6, R513.2
unnamed: P505.1, R521.2
unnamed: P505.3, R522.2
unnamed: P505.5, R523.2
unnamed: P505.7, R524.2, R529.2
unnamed: P505.9, R525.2
unnamed: P505.11, R526.2
unnamed: P505.13, R527.2
unnamed: P505.17, R528.2, R558.2
unnamed: P506.1, R537.1
unnamed: P507.1, R538.1
unnamed: P508.2, P508.4, R543.1
unnamed: P508.12, R544.1
unnamed: P508.13, R541.2
unnamed: P508.35, R542.2
unnamed: P508.38, R545.1
unnamed: P508.40, R546.1
unnamed: R211.1, U202.3
unnamed: R213.1, U201.2
unnamed: R216.1, TR201.1
unnamed: R216.2, TR202.3, TR203.3
unnamed: R217.2, U202.17
unnamed: R218.2, U202.30
unnamed: R219.2, R223.1, TR202.1
unnamed: R221.2, R222.1, TR203.1
unnamed: R226.2, U203.1
unnamed: R227.2, U203.2
unnamed: R228.2, U203.3
unnamed: R233.2, R241.2, U203.7
unnamed: R240.1, TR204.1
unnamed: R242.2, U202.22
unnamed: R243.2, U202.23
unnamed: R407.2, XTAL401.3
unnamed: R409.1, U403.8
unnamed: TP201.1, U202.31
VAA: C323.1, C326.1, C329.1, L204.1, L205.1, U302.5
VCC: C301.2, C302.2, C304.1, C306.2, C307.2, C308.1, L301.2, R302.1, R305.1, R310.1, U301.1
VDD: C325.1, C328.1, C331.1, L201.1, U304.5
VPP: C249.1, C324.1, C327.1, C330.1, D503.2, D504.2, L202.1, L203.1, L401.1, L402.1, R219.1, R221.1, R224.1, R236.1, R237.1, TR202.2, TR203.2, U303.5
